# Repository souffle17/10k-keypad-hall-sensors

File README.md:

# 10k-keypad with variable input hall sensors

A 2x5 mechanical keypad circuit and PCB. The second row is made to support hall-effect switches with variable input, similar to those on rapid trigger/wooting keyboards, in addition to normal switches.          

Footprint "SW_MX_HS_CPG151101S11_1u_no_center" is modified from marbastlib's "SW_MX_HS_CPG151101S11_1u"

### Helpful resources:
- https://guide.zykrah.me/
- https://www.masterzen.fr/2020/05/03/designing-a-keyboard-part-1/
- https://wiki.ai03.com/books/pcb-design/chapter/pcb-designer-guide

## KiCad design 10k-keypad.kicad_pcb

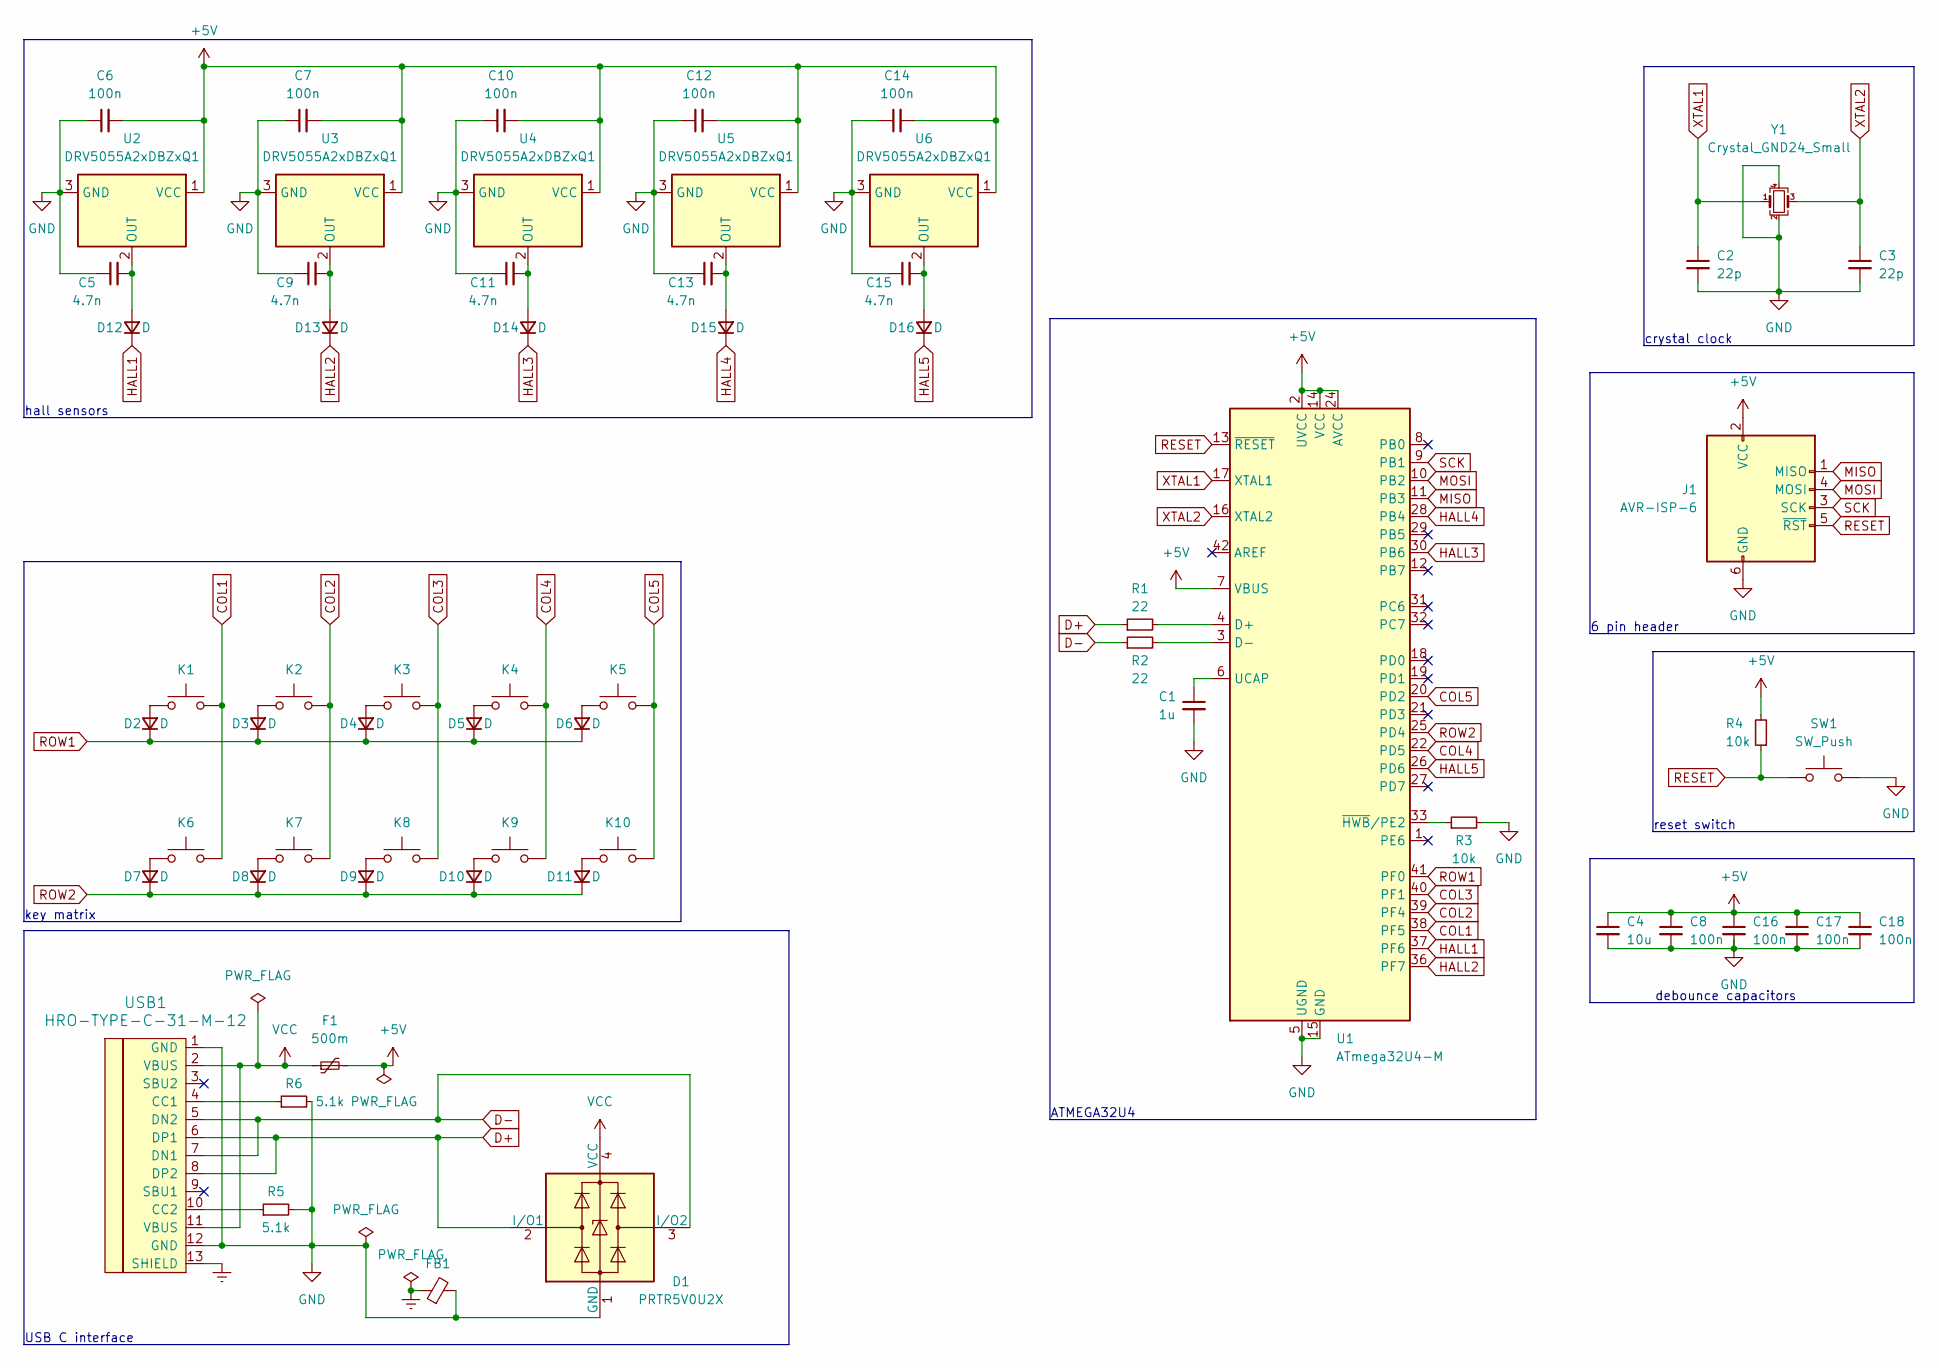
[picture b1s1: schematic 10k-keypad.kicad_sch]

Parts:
C1: 1u; C_0805_2012Metric_Pad1.18x1.45mm_HandSolder
C2, C3: 22p; C_0805_2012Metric_Pad1.18x1.45mm_HandSolder
C4: 10u; C_0805_2012Metric_Pad1.18x1.45mm_HandSolder
C5, C9, C11, C13, C15: 4.7n; C_0805_2012Metric_Pad1.18x1.45mm_HandSolder
C6, C7, C8, C10, C12, C14, C16, C17, C18: 100n; C_0805_2012Metric_Pad1.18x1.45mm_HandSolder
D1: PRTR5V0U2X; SOT-143
D2, D3, D4, D5, D6, D7, D8, D9, D10, D11, D12, D13, D14, D15, D16: D; D_SOD-123
F1: 500m; Fuse_1206_3216Metric_Pad1.42x1.75mm_HandSolder
FB1: FerriteBead_Small; L_0805_2012Metric_Pad1.15x1.40mm_HandSolder
J1: AVR-ISP-6; Reset_Pretty-Mask
K1, K2, K3, K4, K5: SW_Push; SW_MX_HS_CPG151101S11_1u
K6, K7, K8, K9, K10: SW_Push; SW_MX_HS_CPG151101S11_1u_no_center
R1, R2: 22; R_0805_2012Metric_Pad1.20x1.40mm_HandSolder
R3, R4: 10k; R_0805_2012Metric_Pad1.20x1.40mm_HandSolder
R5, R6: 5.1k; R_0805_2012Metric_Pad1.20x1.40mm_HandSolder
SW1: SW_Push; SW_SPST_SKQG_WithStem
U1: ATmega32U4-M; QFN-44-1EP_7x7mm_P0.5mm_EP5.2x5.2mm
U2, U3, U4, U5, U6: DRV5055A2xDBZxQ1; SOT-23
USB1: HRO-TYPE-C-31-M-12; HRO-TYPE-C-31-M-12-HandSoldering
Y1: Crystal_GND24_Small; Crystal_SMD_3225-4Pin_3.2x2.5mm_HandSoldering

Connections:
+5V: C4.1, C6.2, C7.2, C8.1, C10.2, C12.2, C14.2, C16.1, C17.1, C18.1, F1.2, J1.2 (VCC), R4.2, U1.2 (UVCC), U1.7 (VBUS), U1.14 (VCC), U1.24 (AVCC), U1.34 (VCC), U1.44 (AVCC), U2.1 (VCC), U3.1 (VCC), U4.1 (VCC), U5.1 (VCC), U6.1 (VCC)
COL1: K1.2, K6.2, U1.38 (PF5)
COL2: K2.2, K7.2, U1.39 (PF4)
COL3: K3.2, K8.2, U1.40 (PF1)
COL4: K4.2, K9.2, U1.22 (PD5)
COL5: K5.2, K10.2, U1.20 (PD2)
D+: D1.2 (I/O1), R1.1, USB1.6 (DP1), USB1.8 (DP2)
D-: D1.3 (I/O2), R2.1, USB1.5 (DN2), USB1.7 (DN1)
Earth: FB1.1, USB1.13 (SHIELD)
GND: C1.2, C2.2, C3.2, C4.2, C5.1, C6.1, C7.1, C8.2, C9.1, C10.1, C11.1, C12.1, C13.1, C14.1, C15.1, C16.2, C17.2, C18.2, D1.1 (GND), FB1.2, J1.6 (GND), R3.2, R5.2, R6.2, SW1.2, U1.5 (UGND), U1.15 (GND), U1.23 (GND), U1.35 (GND), U1.43 (GND), U1.45 (GND), U2.3 (GND), U3.3 (GND), U4.3 (GND), U5.3 (GND), U6.3 (GND), USB1.1 (GND), USB1.12 (GND), Y1.2, Y1.4
HALL1: D12.1 (K), U1.37 (PF6)
HALL2: D13.1 (K), U1.36 (PF7)
HALL3: D14.1 (K), U1.30 (PB6)
HALL4: D15.1 (K), U1.28 (PB4)
HALL5: D16.1 (K), U1.26 (PD6)
MISO: J1.1 (MISO), U1.11 (PB3)
MOSI: J1.4 (MOSI), U1.10 (PB2)
unnamed: D2.2 (A), K1.1
unnamed: D3.2 (A), K2.1
unnamed: D4.2 (A), K3.1
unnamed: D5.2 (A), K4.1
unnamed: D6.2 (A), K5.1
unnamed: D7.2 (A), K6.1
unnamed: D8.2 (A), K7.1
unnamed: D9.2 (A), K8.1
unnamed: D10.2 (A), K9.1
unnamed: D11.2 (A), K10.1
unnamed: C5.2, D12.2 (A), U2.2 (OUT)
unnamed: C9.2, D13.2 (A), U3.2 (OUT)
unnamed: C11.2, D14.2 (A), U4.2 (OUT)
unnamed: C13.2, D15.2 (A), U5.2 (OUT)
unnamed: C15.2, D16.2 (A), U6.2 (OUT)
unnamed: R1.2, U1.4 (D+)
unnamed: R2.2, U1.3 (D-)
unnamed: C1.1, U1.6 (UCAP)
unnamed: R3.1, U1.33 (~HWB/PE2)
unnamed: R6.1, USB1.4 (CC1)
unnamed: R5.1, USB1.10 (CC2)
RESET: J1.5 (~RST), R4.1, SW1.1, U1.13 (~RESET)
ROW1: D2.1 (K), D3.1 (K), D4.1 (K), D5.1 (K), D6.1 (K), U1.41 (PF0)
ROW2: D7.1 (K), D8.1 (K), D9.1 (K), D10.1 (K), D11.1 (K), U1.25 (PD4)
SCK: J1.3 (SCK), U1.9 (PB1)
VCC: D1.4 (VCC), F1.1, USB1.2 (VBUS), USB1.11 (VBUS)
XTAL1: C2.1, U1.17 (XTAL1), Y1.1
XTAL2: C3.1, U1.16 (XTAL2), Y1.3

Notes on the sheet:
crystal clock
hall sensors
key matrix
ATMEGA32U4
USB C interface
reset switch
6 pin header
debounce capacitors

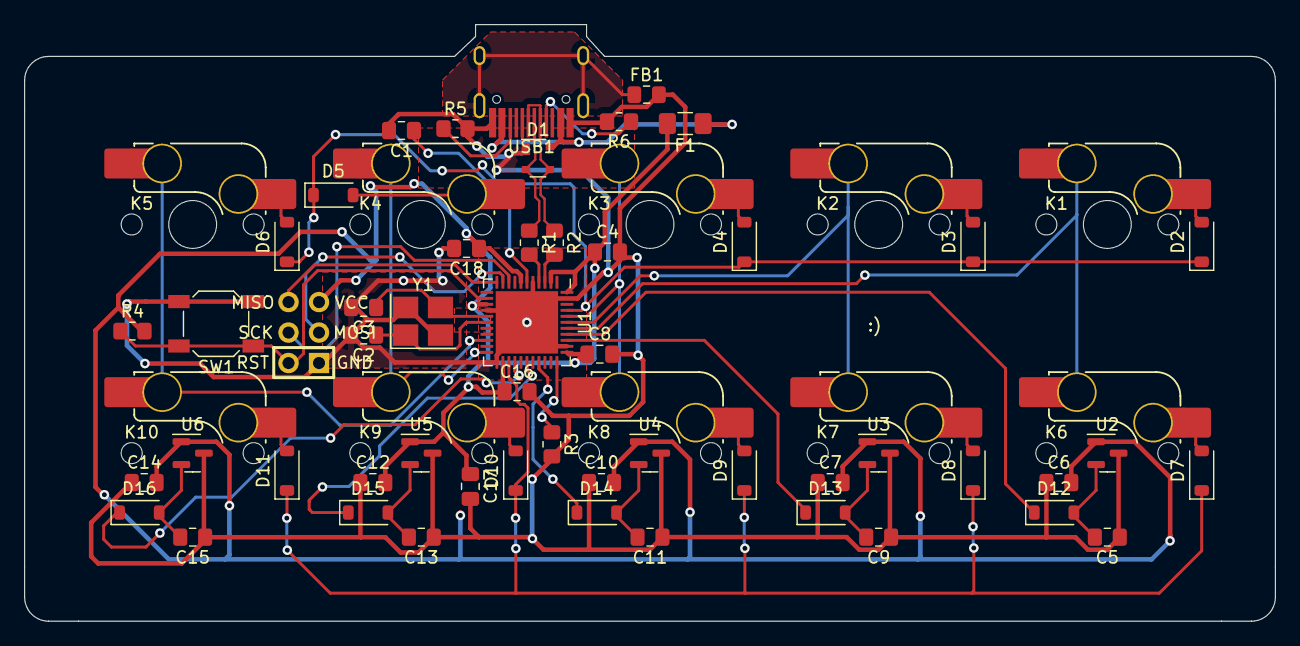
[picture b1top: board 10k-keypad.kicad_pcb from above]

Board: 2 copper layers, 104.2 x 49.7 mm, 62 parts (0 on the bottom side), 45 nets.

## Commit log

2024-03-13 nearly whole schematic
2024-03-13 finish schematic
2024-03-13 footprints
2024-03-13 start pcb
2024-03-13 crystal clock
2024-03-13 finish routing
2024-03-13 board cutout
2024-03-13 readme
2024-03-13 clearance fix
2024-03-13 redundant files
2024-03-13 fix edge cut
2024-03-13 gerbers
2024-03-14 add hall sensors to schematic
2024-03-14 submodule fix
2024-03-14 complete hall sensor schematic
2024-03-14 hall sensor circuitry
2024-03-14 narrower edges, fill fix
2024-03-14 finish pcb
2024-03-15 fix hall sensor circuitry
2024-03-15 drc rules
2024-03-15 fix schematic, gerbers
2024-03-15 fix pcb labels
2024-03-15 Update LICENSE
2024-03-23 redo all routing, remove unused footprint
2024-04-02 new board edge
2024-04-02 remove unused libraries
2024-04-03 fix ground fill
2024-08-20 correct analog pins
2024-09-03 move hall sensors to center
